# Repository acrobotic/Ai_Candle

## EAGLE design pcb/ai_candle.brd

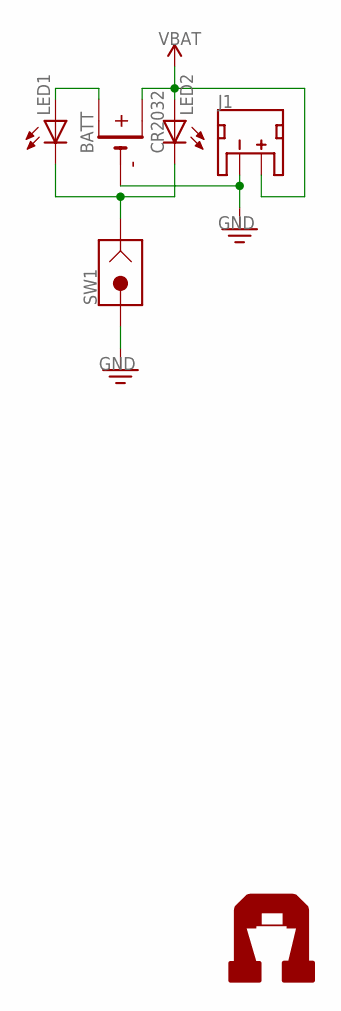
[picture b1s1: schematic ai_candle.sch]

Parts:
BATT: CR2032; CR2032-TH
J1: JST-2-MALE; JST-2P-SMD
LED1, LED2: LED5MM; LED-5MM
SW1: TILT-SW-200D; TILT
U$2: AI-LOGOM; AI-LOGO-M

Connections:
GND: BATT.3 (-), J1.2 (-), SW1.2 (1)
unnamed: BATT.1 (+), LED1.A
unnamed: LED1.C, LED2.C, SW1.1 (2)
VBAT: BATT.2 (+), J1.1 (+), LED2.A

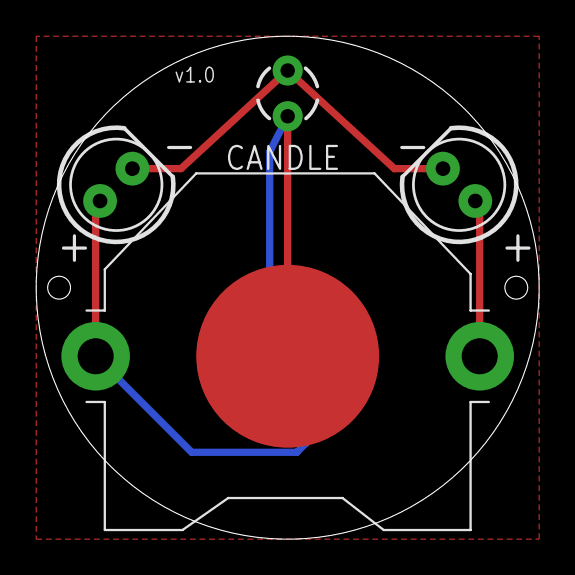
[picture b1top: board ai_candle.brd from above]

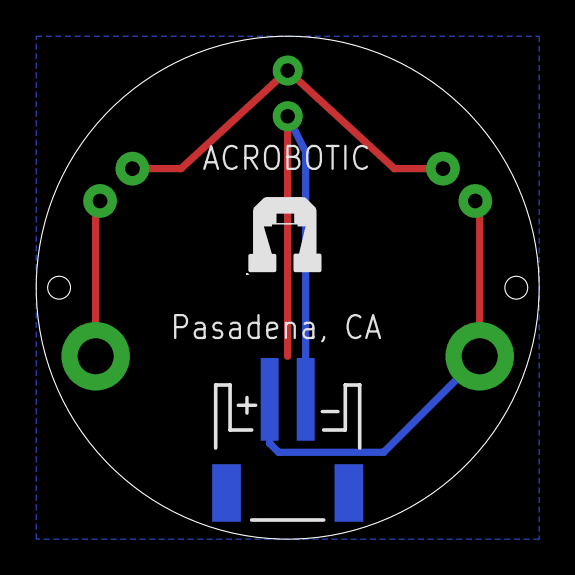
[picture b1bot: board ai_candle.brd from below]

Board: 2 copper layers, 27.9 x 27.9 mm, 6 parts (2 on the bottom side), 4 nets.

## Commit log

2014-11-27 ready for manufacturing
2014-12-02 updating
